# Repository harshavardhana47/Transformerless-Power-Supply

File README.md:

Transformerless Power Supply (5V Output) – KiCad Design

Designed a compact transformerless AC to DC power supply delivering regulated 5V output using KiCad, optimized for low-cost and space-constrained applications.

🔌 Implemented capacitive dropper circuit for voltage reduction
🔁 Used bridge rectifier (1N4007 diodes) for AC to DC conversion
⚡ Integrated filter capacitors for ripple minimization
🎯 Added Zener diode regulation + LM7805 for stable 5V output
💡 Included LED indicator for power status
✅ Verified using ERC (0 errors) ensuring schematic reliability

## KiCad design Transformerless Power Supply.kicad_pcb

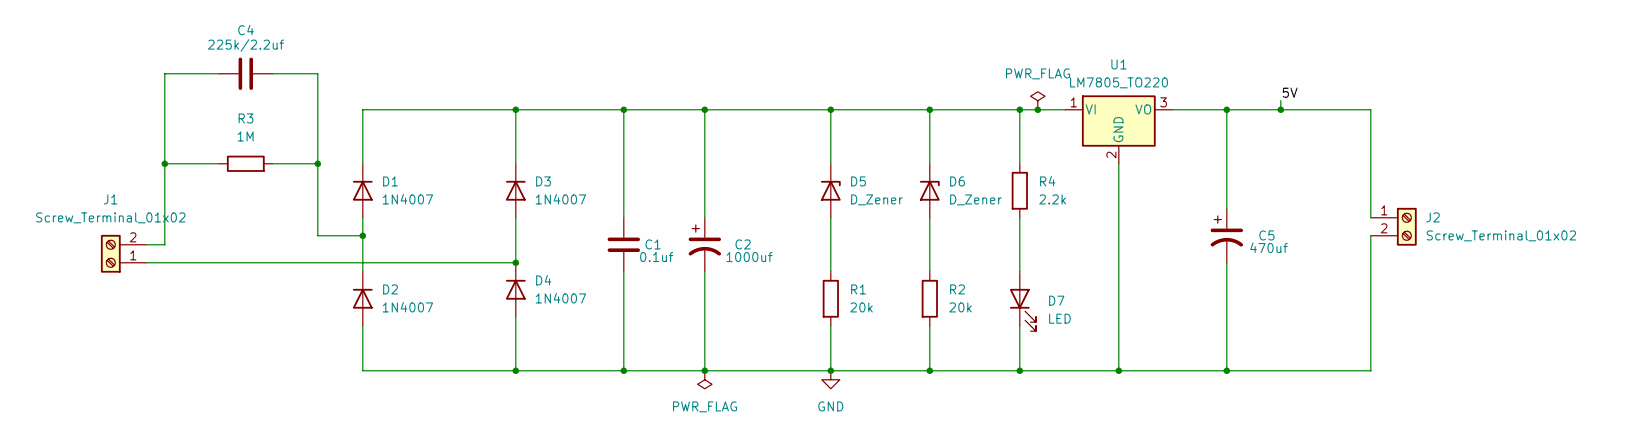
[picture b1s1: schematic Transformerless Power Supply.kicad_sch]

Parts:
C1: 0.1uf; C_Disc_D4.7mm_W2.5mm_P5.00mm
C2: 1000uf; CP_Radial_D10.0mm_P3.80mm
C4: 225k/2.2uf; C_Rect_L18.0mm_W6.0mm_P15.00mm_FKS3_FKP3
C5: 470uf; CP_Radial_D10.0mm_P3.80mm
D1, D2, D3, D4: 1N4007; D_DO-41_SOD81_P10.16mm_Horizontal
D5, D6: D_Zener; D_A-405_P7.62mm_Horizontal
D7: LED; LED_D5.0mm
J1, J2: Screw_Terminal_01x02; TerminalBlock_MaiXu_MX126-5.0-02P_1x02_P5.00mm
R1, R2: 20k; R_Axial_DIN0207_L6.3mm_D2.5mm_P7.62mm_Horizontal
R3: 1M; R_Axial_DIN0207_L6.3mm_D2.5mm_P7.62mm_Horizontal
R4: 2.2k; R_Axial_DIN0207_L6.3mm_D2.5mm_P7.62mm_Horizontal
U1: LM7805_TO220; TO-220-3_Vertical

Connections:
/5V: C5.1, J2.1, U1.3 (VO)
GND: C1.2, C2.2, C5.2, D2.2 (A), D4.2 (A), D7.1 (K), J2.2, R1.2, R2.2, U1.2 (GND)
unnamed: C4.2, D1.2 (A), D2.1 (K), R3.2
unnamed: C1.1, C2.1, D1.1 (K), D3.1 (K), D5.1 (K), D6.1 (K), R4.1, U1.1 (VI)
unnamed: D3.2 (A), D4.1 (K), J1.1
unnamed: D5.2 (A), R1.1
unnamed: D6.2 (A), R2.1
unnamed: D7.2 (A), R4.2
unnamed: C4.1, J1.2, R3.1

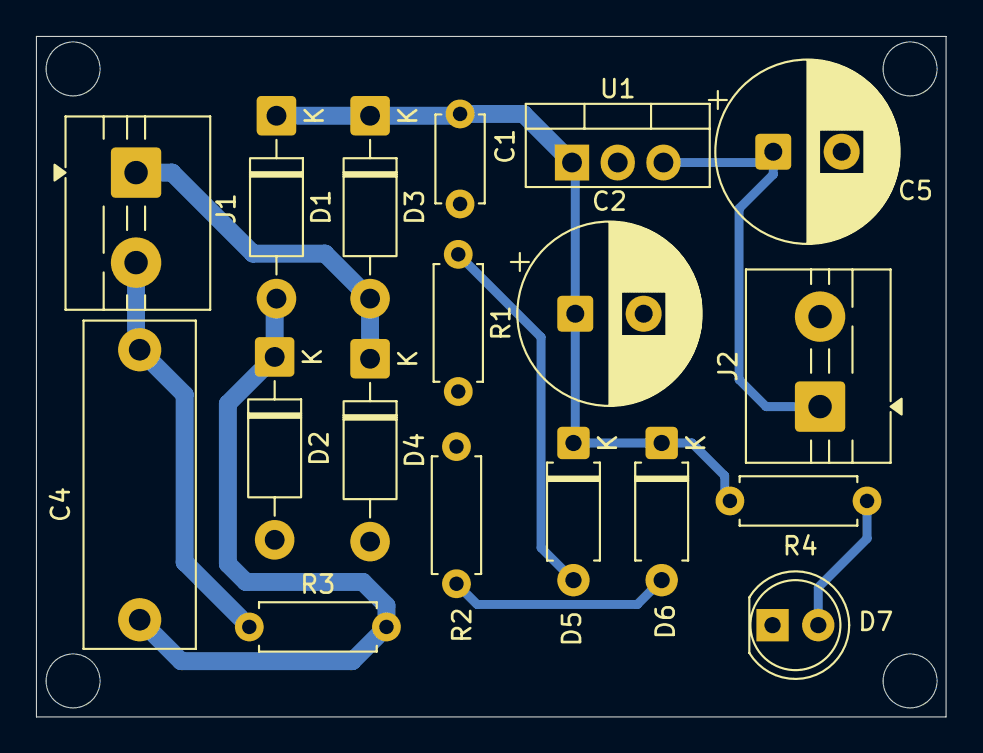
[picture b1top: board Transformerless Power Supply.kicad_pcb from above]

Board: 2 copper layers, 50.5 x 37.8 mm, 18 parts (0 on the bottom side), 9 nets.
